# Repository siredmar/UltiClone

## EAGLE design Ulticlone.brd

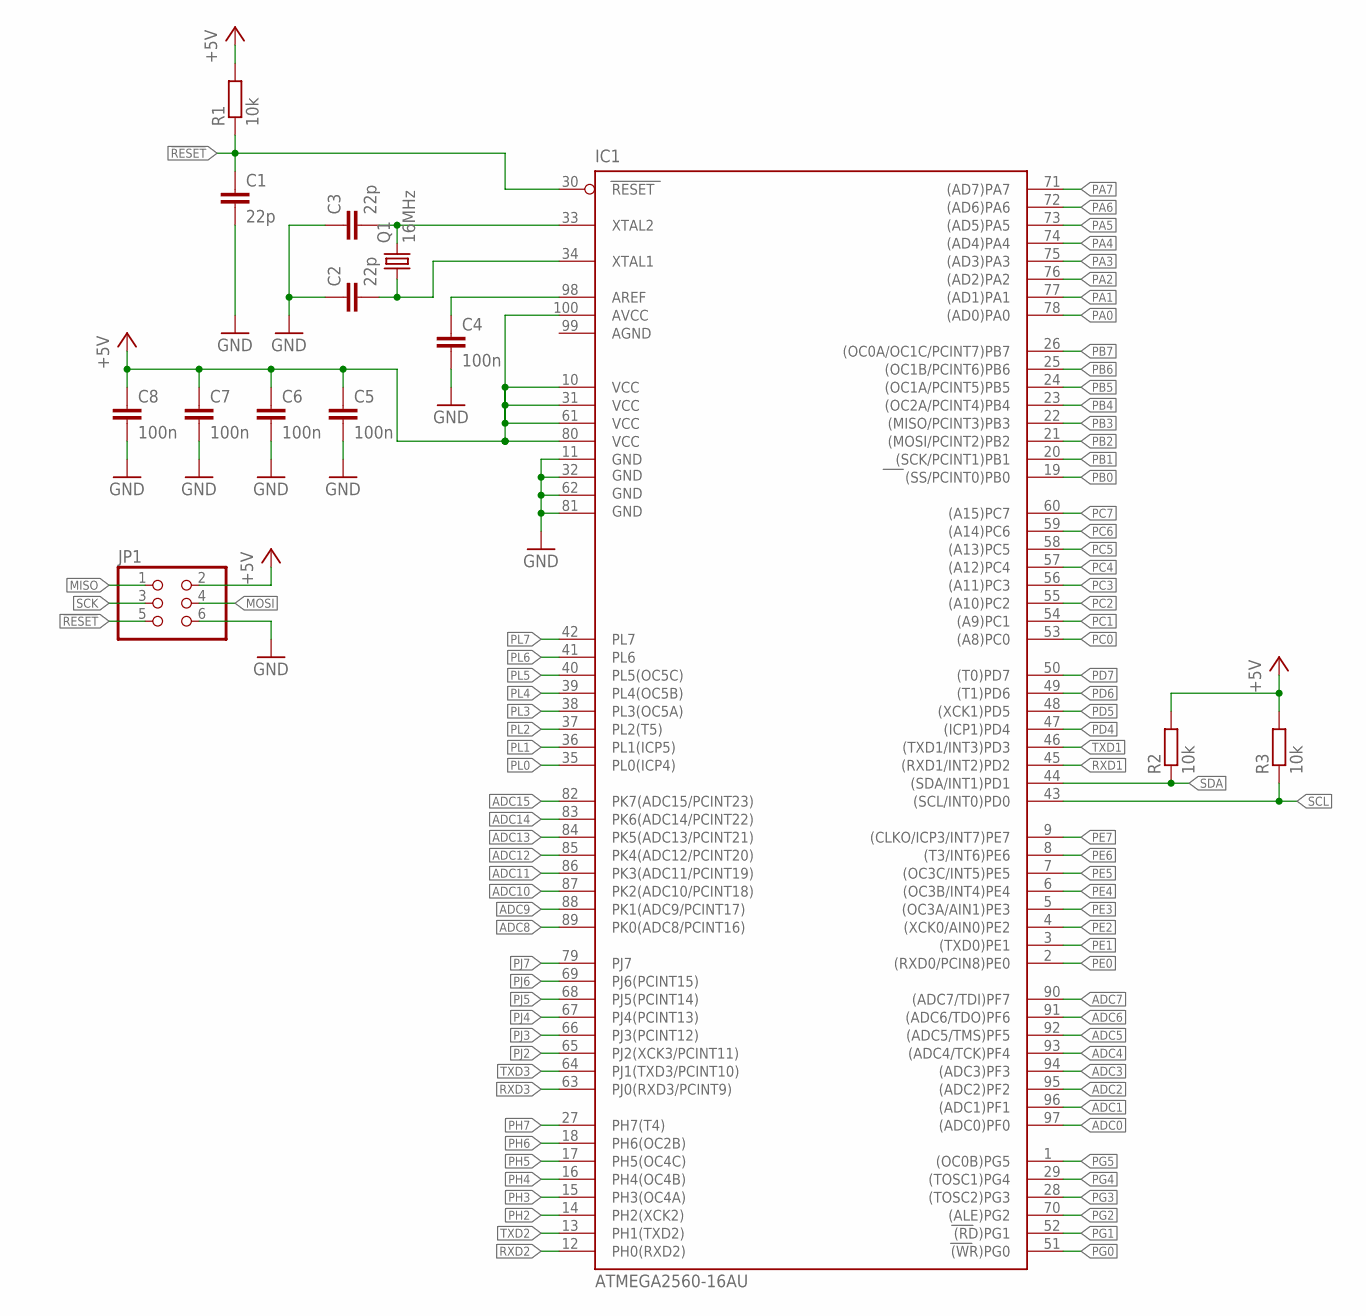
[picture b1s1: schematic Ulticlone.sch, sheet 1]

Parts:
C1, C2, C3: 22p; C0603K
C4, C5, C6, C7, C8: 100n; C0603K
IC1: ATMEGA2560-16AU; TQFP100
JP1: PINHD-2X3; 2X03
Q1: 16MHz; HC49UP
R1, R2, R3: 10k; R0603

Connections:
!RESET: C1.1, IC1.30 (RESET), JP1.5, R1.1
+5V: C5.1, C6.1, C7.1, C8.1, IC1.10 (VCC), IC1.31 (VCC1), IC1.61 (VCC2), IC1.80 (VCC3), IC1.100 (AVCC), JP1.2, R1.2, R2.2, R3.2; also elsewhere on the board
ADC0: IC1.97 ((ADC0)PF0)
ADC1: IC1.96 ((ADC1)PF1)
ADC2: IC1.95 ((ADC2)PF2)
ADC3: IC1.94 ((ADC3)PF3)
ADC4: IC1.93 ((ADC4/TCK)PF4)
ADC5: IC1.92 ((ADC5/TMS)PF5)
ADC6: IC1.91 ((ADC6/TDO)PF6)
ADC7: IC1.90 ((ADC7/TDI)PF7)
ADC8: IC1.89 (PK0(ADC8/PCINT16)); also elsewhere on the board
ADC9: IC1.88 (PK1(ADC9/PCINT17)); also elsewhere on the board
ADC10: IC1.87 (PK2(ADC10/PCINT18)); also elsewhere on the board
ADC11: IC1.86 (PK3(ADC11/PCINT19))
ADC12: IC1.85 (PK4(ADC12/PCINT20))
ADC13: IC1.84 (PK5(ADC13/PCINT21))
ADC14: IC1.83 (PK6(ADC14/PCINT22)); also elsewhere on the board
ADC15: IC1.82 (PK7(ADC15/PCINT23)); also elsewhere on the board
AGND: IC1.99 (AGND)
GND: C1.2, C2.1, C3.1, C4.2, C5.2, C6.2, C7.2, C8.2, IC1.11 (GND), IC1.32 (GND1), IC1.62 (GND2), IC1.81 (GND3), JP1.6; also elsewhere on the board
MISO: JP1.1
MOSI: JP1.4
unnamed: C3.2, IC1.33 (XTAL2), Q1.2
unnamed: C2.2, IC1.34 (XTAL1), Q1.1
unnamed: C4.1, IC1.98 (AREF)
PA0: IC1.78 ((AD0)PA0); also elsewhere on the board
PA1: IC1.77 ((AD1)PA1)
PA2: IC1.76 ((AD2)PA2)
PA3: IC1.75 ((AD3)PA3)
PA4: IC1.74 ((AD4)PA4); also elsewhere on the board
PA5: IC1.73 ((AD5)PA5)
PA6: IC1.72 ((AD6)PA6)
PA7: IC1.71 ((AD7)PA7); also elsewhere on the board
PB0: IC1.19 ((SS/PCINT0)PB0)
PB1: IC1.20 ((SCK/PCINT1)PB1)
PB2: IC1.21 ((MOSI/PCINT2)PB2)
PB3: IC1.22 ((MISO/PCINT3)PB3)
PB4: IC1.23 ((OC2A/PCINT4)PB4)
PB5: IC1.24 ((OC1A/PCINT5)PB5)
PB6: IC1.25 ((OC1B/PCINT6)PB6)
PB7: IC1.26 ((OC0A/OC1C/PCINT7)PB7)
PC0: IC1.53 ((A8)PC0)
PC1: IC1.54 ((A9)PC1)
PC2: IC1.55 ((A10)PC2)
PC3: IC1.56 ((A11)PC3)
PC4: IC1.57 ((A12)PC4)
PC5: IC1.58 ((A13)PC5)
PC6: IC1.59 ((A14)PC6)
PC7: IC1.60 ((A15)PC7)
PD4: IC1.47 ((ICP1)PD4)
PD5: IC1.48 ((XCK1)PD5)
PD6: IC1.49 ((T1)PD6)
PD7: IC1.50 ((T0)PD7)
PE0: IC1.2 ((RXD0/PCIN8)PE0)
PE1: IC1.3 ((TXD0)PE1)
PE2: IC1.4 ((XCK0/AIN0)PE2)
PE3: IC1.5 ((OC3A/AIN1)PE3)
PE4: IC1.6 ((OC3B/INT4)PE4)
PE5: IC1.7 ((OC3C/INT5)PE5)
PE6: IC1.8 ((T3/INT6)PE6)
PE7: IC1.9 ((CLKO/ICP3/INT7)PE7)
PG0: IC1.51 ((WR)PG0)
PG1: IC1.52 ((RD)PG1)
PG2: IC1.70 ((ALE)PG2)
PG3: IC1.28 ((TOSC2)PG3)
PG4: IC1.29 ((TOSC1)PG4)
PG5: IC1.1 ((OC0B)PG5)
PH2: IC1.14 (PH2(XCK2))
PH3: IC1.15 (PH3(OC4A))
PH4: IC1.16 (PH4(OC4B)); also elsewhere on the board
PH5: IC1.17 (PH5(OC4C)); also elsewhere on the board
PH6: IC1.18 (PH6(OC2B))
PH7: IC1.27 (PH7(T4))
PJ2: IC1.65 (PJ2(XCK3/PCINT11))
PJ3: IC1.66 (PJ3(PCINT12))
PJ4: IC1.67 (PJ4(PCINT13))
PJ5: IC1.68 (PJ5(PCINT14))
PJ6: IC1.69 (PJ6(PCINT15))
PJ7: IC1.79 (PJ7)
PL0: IC1.35 (PL0(ICP4))
PL1: IC1.36 (PL1(ICP5))
PL2: IC1.37 (PL2(T5))
PL3: IC1.38 (PL3(OC5A))
PL4: IC1.39 (PL4(OC5B))
PL5: IC1.40 (PL5(OC5C))
PL6: IC1.41 (PL6)
PL7: IC1.42 (PL7)
RXD1: IC1.45 ((RXD1/INT2)PD2)
RXD2: IC1.12 (PH0(RXD2))
RXD3: IC1.63 (PJ0(RXD3/PCINT9))
SCK: JP1.3
SCL: IC1.43 ((SCL/INT0)PD0), R3.1
SDA: IC1.44 ((SDA/INT1)PD1), R2.1
TXD1: IC1.46 ((TXD1/INT3)PD3)
TXD2: IC1.13 (PH1(TXD2))
TXD3: IC1.64 (PJ1(TXD3/PCINT10))

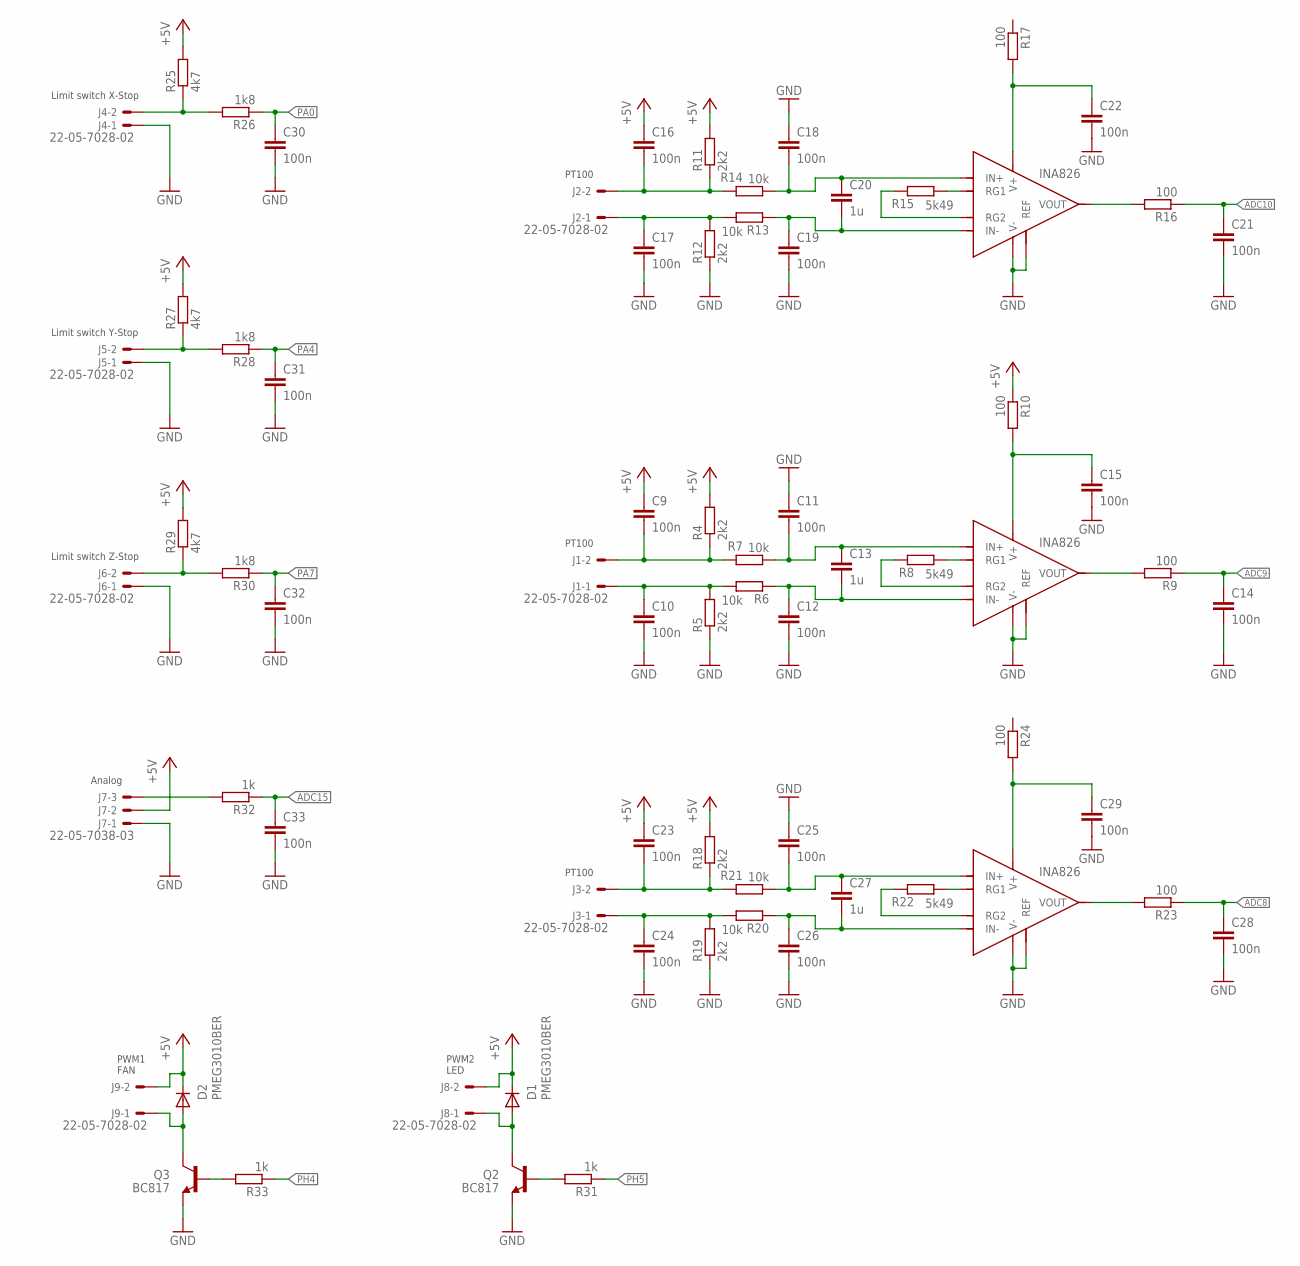
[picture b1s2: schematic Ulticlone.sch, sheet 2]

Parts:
C9, C10, C11, C12, C14, C15, C16, C17, C18, C19, C21, C22, C23, C24, C25, C26, C28, C29, C30, C31, C32, C33: 100n; C0603K
C13, C20, C27: 1u; C0805K
D1, D2: PMEG3010BER; SOD123
J1, J2, J3, J4, J5, J6, J8, J9: 22-05-7028-02; 7395-02
J7: 22-05-7038-03; 7395-03
Q2, Q3: BC817; SOT23-BEC
R4, R5, R11, R12, R18, R19: 2k2; R0603
R6, R7, R13, R14, R20, R21: 10k; R0603
R8, R15, R22: 5k49; R0603
R9, R10, R16, R17, R23, R24: 100; R0603
R25, R27, R29: 4k7; R0603
R26, R28, R30: 1k8; R0603
R31, R32, R33: 1k; R0603
U1, U2, U3: INA826; SO-8

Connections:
+5V: C9.1, C16.1, C23.1, D1.C, D2.C, J7.2, J8.2, J9.2, R4.2, R10.1, R11.2, R18.2, R25.2, R27.2, R29.2; also elsewhere on the board
ADC8: C28.1, R23.1; also elsewhere on the board
ADC9: C14.1, R9.1; also elsewhere on the board
ADC10: C21.1, R16.1; also elsewhere on the board
ADC15: C33.1, R32.1; also elsewhere on the board
GND: C10.2, C11.1, C12.2, C14.2, C15.2, C17.2, C18.1, C19.2, C21.2, C22.2, C24.2, C25.1, C26.2, C28.2, C29.2, C30.2, C31.2, C32.2, C33.2, J4.1, J5.1, J6.1, J7.1, Q2.E, Q3.E, R5.1, R12.1, R19.1, U1.P$5 (V-), U1.P$6 (REF), U2.P$5 (V-), U2.P$6 (REF), U3.P$5 (V-), U3.P$6 (REF); also elsewhere on the board
unnamed: C9.2, J1.2, R4.1, R7.2
unnamed: R8.2, U1.P$3 (RG2)
unnamed: C10.1, J1.1, R5.2, R6.2
unnamed: C11.2, C13.1, R7.1, U1.P$4 (IN+)
unnamed: C12.1, C13.2, R6.1, U1.P$1 (IN-)
unnamed: R8.1, U1.P$2 (RG1)
unnamed: R9.2, U1.P$7 (VOUT)
unnamed: C15.1, R10.2, U1.P$8 (V+)
unnamed: J4.2, R25.1, R26.2
unnamed: J7.3, R32.2
unnamed: J5.2, R27.1, R28.2
unnamed: J6.2, R29.1, R30.2
unnamed: C16.2, J2.2, R11.1, R14.2
unnamed: C17.1, J2.1, R12.2, R13.2
unnamed: C18.2, C20.1, R14.1, U2.P$4 (IN+)
unnamed: C19.1, C20.2, R13.1, U2.P$1 (IN-)
unnamed: R15.1, U2.P$2 (RG1)
unnamed: R15.2, U2.P$3 (RG2)
unnamed: R16.2, U2.P$7 (VOUT)
unnamed: C22.1, R17.2, U2.P$8 (V+)
unnamed: C23.2, J3.2, R18.1, R21.2
unnamed: C24.1, J3.1, R19.2, R20.2
unnamed: C25.2, C27.1, R21.1, U3.P$4 (IN+)
unnamed: C26.1, C27.2, R20.1, U3.P$1 (IN-)
unnamed: R22.1, U3.P$2 (RG1)
unnamed: R22.2, U3.P$3 (RG2)
unnamed: R23.2, U3.P$7 (VOUT)
unnamed: C29.1, R24.2, U3.P$8 (V+)
unnamed: D1.A, J8.1, Q2.C
unnamed: Q2.B, R31.2
unnamed: D2.A, J9.1, Q3.C
unnamed: Q3.B, R33.2
PA0: C30.1, R26.1; also elsewhere on the board
PA4: C31.1, R28.1; also elsewhere on the board
PA7: C32.1, R30.1; also elsewhere on the board
PH4: R33.1; also elsewhere on the board
PH5: R31.1; also elsewhere on the board

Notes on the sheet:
PT100
Analog
Limit switch Z-Stop
Limit switch Y-Stop
Limit switch X-Stop
PWM1 FAN
PWM2 LED

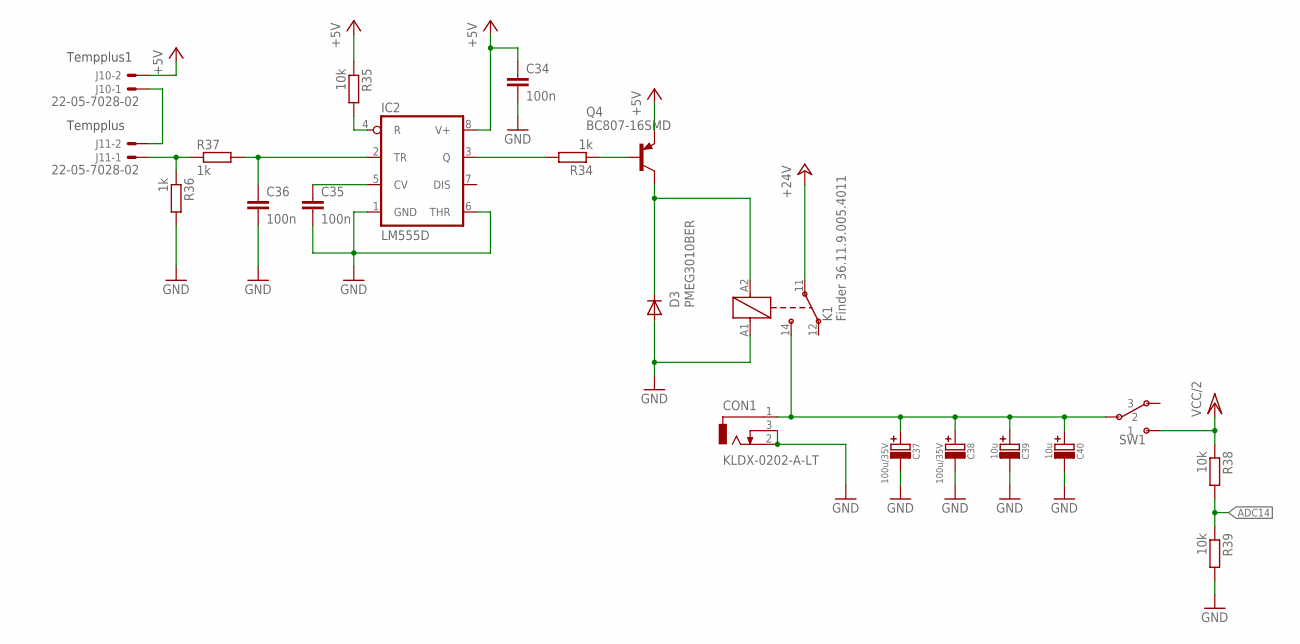
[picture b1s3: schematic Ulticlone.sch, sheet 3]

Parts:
C34, C35, C36: 100n; C0603K
C37, C38: 100u/35V; C_POL_4X4MM
C39, C40: 10u; C_POL_4X4MM
CON1: KLDX-0202-A-LT
D3: PMEG3010BER; SOD123
IC2: LM555D; SO08
J10, J11: 22-05-7028-02; 7395-02
K1: Finder 36.11.9.005.4011; 36.11
Q4: BC807-16SMD; SOT23-BEC
R34, R36, R37: 1k; R0603
R35, R38, R39: 10k; R0603
SW1: SW-SPDT-4MS1R202BM6NQNS

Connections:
+5V: C34.1, IC2.8 (V+), J10.2, Q4.E, R35.1; also elsewhere on the board
+24V: K1.11
ADC14: R38.2, R39.1; also elsewhere on the board
GND: C34.2, C35.2, C36.2, C37.-, C38.-, C39.-, C40.-, CON1.2 (3), CON1.3 (2), D3.A, IC2.1 (GND), IC2.6 (THR), K1.A1, R36.2, R39.2; also elsewhere on the board
unnamed: D3.C, K1.A2 (1), Q4.C
unnamed: J10.1, J11.2
unnamed: C37.+, C38.+, C39.+, C40.+, CON1.1, K1.14, SW1.2
unnamed: C35.1, IC2.5 (CV)
unnamed: C36.1, IC2.2 (TR), R37.2
unnamed: J11.1, R36.1, R37.1
unnamed: IC2.4 (R), R35.2
unnamed: IC2.3 (Q), R34.2
unnamed: Q4.B, R34.1
VCC/2: R38.1, SW1.1

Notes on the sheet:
Tempplus1
Tempplus

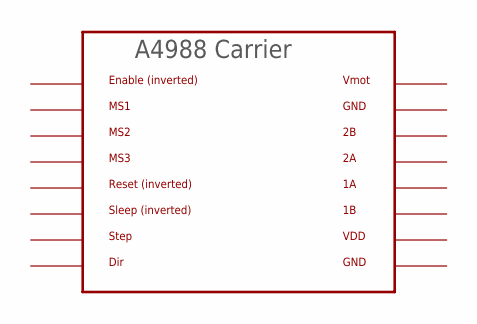
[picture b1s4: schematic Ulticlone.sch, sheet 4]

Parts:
U$1: A4983CARRIER; A4988BREAKOUT

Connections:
GND: U$1.GND, U$1.GND@0 (GND); also elsewhere on the board
VDD: U$1.VDD
VMOT: U$1.VMOT

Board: 2 copper layers, 107 parts (0 on the bottom side), 60 nets, no tracks yet.

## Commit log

2017-12-14 Intermediate work creating schematic
